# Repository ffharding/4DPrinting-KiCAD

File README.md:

# 4DPrinting KiCAD Repository
The objective of the repository is to store the files needed to implement KiCAD automating into the design flow of the 4DPrinting project, including code to automatically generate files and custom components.

## Features 
### 1. kicad-import
This features consist on the code required to import the user input such as the components chosen by the user, the desired placement of these components and the information that relate the components (what the final PCB is designed for). The output of this feature is the base KICAD file that starts the automating design flow.
### 2. autorouting
Autoroute the PCB created using the freerouting open source module and automate the creation of the finished PCB that will be printed.
### 3. xml-generator
Generate an XML file with the already finished and autorouted PCB for better data management.
### 4. gcode-generator
Generate GCODE from the XML file with PCB data.

## Components
### 4DPrinting.pretty
The .pretty folder is a KiCAD library containing custom component footprints created for the base schematic of the projcet, inlcuding components designed to be printed and those components that were modified to fit the specifications of the project (through hole to surface mount components). 

| Component      | Description |
| ------------- |:-------------:|
| Battery.kicad_mod      | Footprint for battery cell pack connected with flywires to +/- pads     |
| MODULE_ESP-M2.kicad_mod      | Footprint for ESP-M2 wifi chip downloaded from SnapEDA: https://www.snapeda.com/parts/ESP-M2/Doctors%20of%20Intelligence%20%26%20Technology%20Co.%2C%20LTD/view-part/?ref=search&t=%20ESP-M2%20    |
| TPU.kicad_mod      | Footprint for printed unit TPU   |
| charge_port.kicad_mod      | Footprint for 3.5mm charging port for battery   |
| custom_lf356.kicad_mod      | Footprint for LF356 chip converted to surface mount device |
| switch.kicad_mod      | Footprint for push button switch |
| voltage_regulator.kicad_mod      | Footprint for LD1117v33 voltage regulator converted to surface mount device |

## Installation
Clone repository into local machine using the following commmands in terminal or Git Bash:
```
git clone https://github.com/ffharding/4DPrinting-KiCAD.git
```
More information into Git repositories can be found on the [offical Git documentation](https://docs.github.com/en/repositories).

After cloning the repository and installing the required software([KiCAD 6.0](https://www.kicad.org/download/) and [freerouting](https://github.com/freerouting/freerouting/releases
)), open the plugin directory from KiCAD using the instructions included in the documentation folder and copy the source code of the feature to test.

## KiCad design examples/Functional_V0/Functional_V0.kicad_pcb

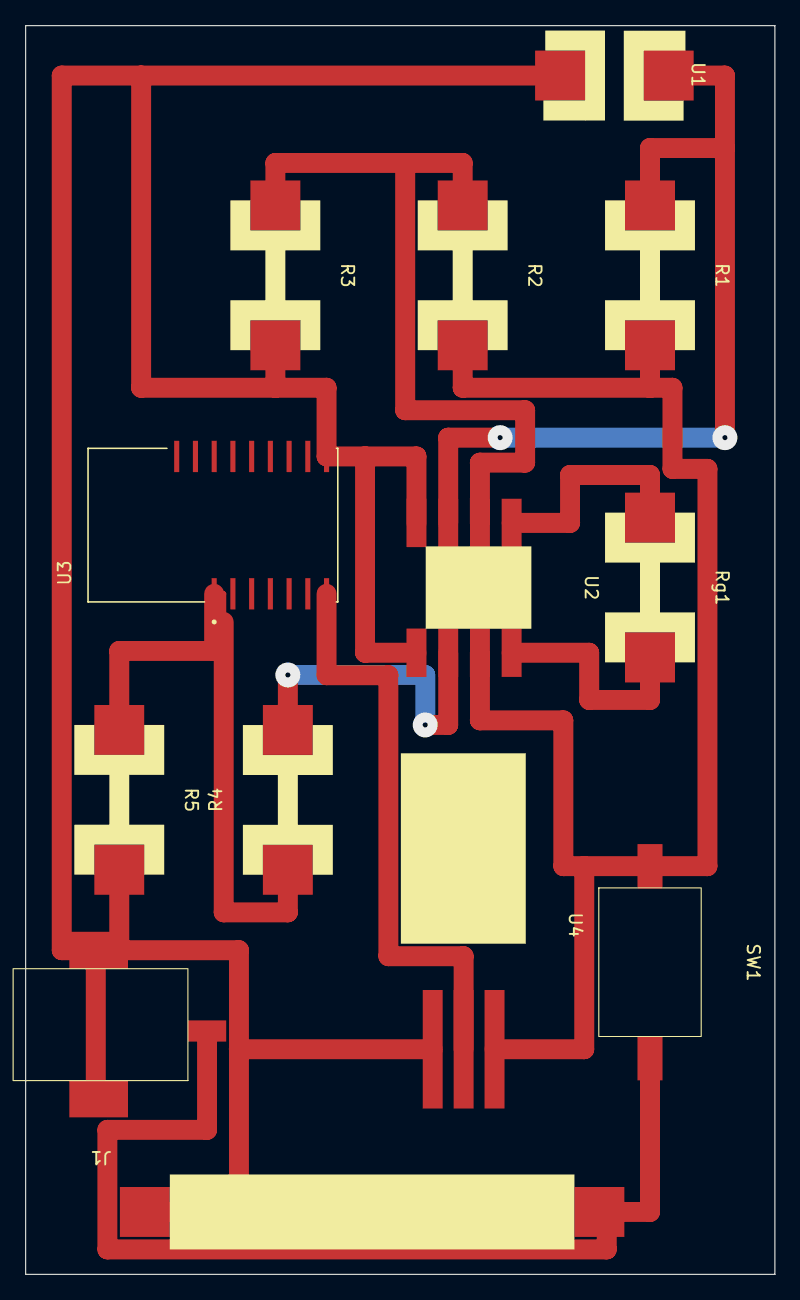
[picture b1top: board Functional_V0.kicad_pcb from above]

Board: 2 copper layers, 60.0 x 100.0 mm, 13 parts (0 on the bottom side), 10 nets.

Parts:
BT1: Battery
J1: charge_port
R1, R2, R3, R4, R5: TPU
Rg1: TPU
SW1: switch
U1: for_thing; wave_gen
U2: dummy_lf356; custom_lf356
U3: MODULE_ESP-M2
U4: voltage_regulator

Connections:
unnamed: BT1.1, J1.1, SW1.2
unnamed: BT1.2, J1.2, J1.3, R3.2, R5.2, U1.1, U2.4, U2.5, U3.8, U4.1
unnamed: R1.1, U1.2, U2.3
unnamed: R1.2, R2.2, SW1.1, U2.7, U4.3
unnamed: R2.1, R3.1, U2.2
unnamed: R4.1, R5.1, U3.1
unnamed: R4.2, U2.6
unnamed: Rg1.1, U2.1
unnamed: Rg1.2, U2.8
unnamed: U3.7, U4.2

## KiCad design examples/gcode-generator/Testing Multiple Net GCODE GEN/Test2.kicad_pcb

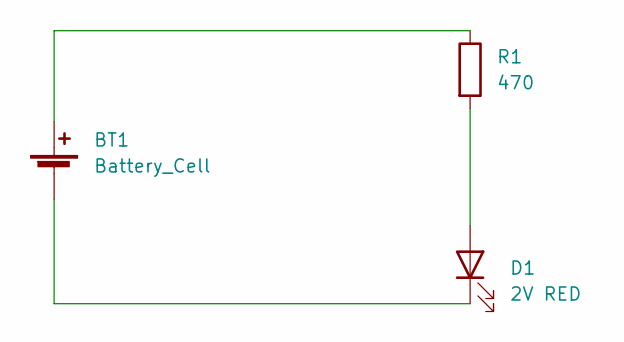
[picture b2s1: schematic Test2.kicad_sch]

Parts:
BT1: Battery_Cell; BatteryHolder_Keystone_1058_1x2032
D1: 2V RED; LED_0603_1608Metric
R1: 470; R_0402_1005Metric

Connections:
unnamed: BT1.2 (-), D1.1 (K)
unnamed: D1.2 (A), R1.2
unnamed: BT1.1 (+), R1.1

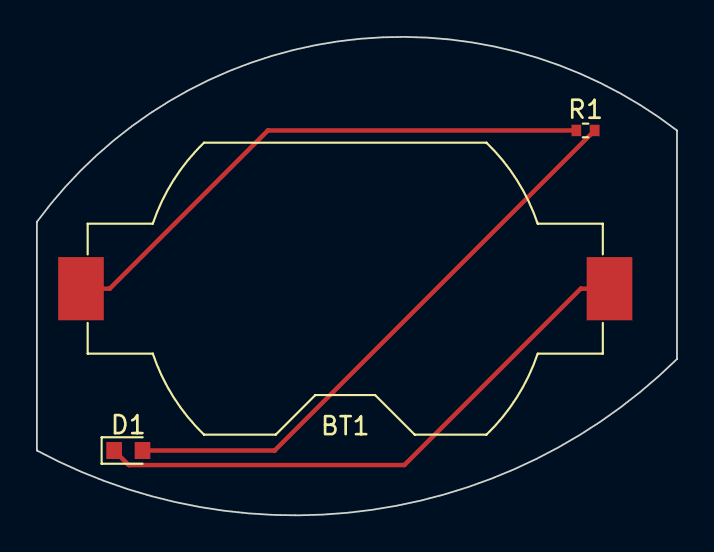
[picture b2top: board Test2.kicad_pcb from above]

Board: 2 copper layers, 35.6 x 26.6 mm, 3 parts (0 on the bottom side), 3 nets.

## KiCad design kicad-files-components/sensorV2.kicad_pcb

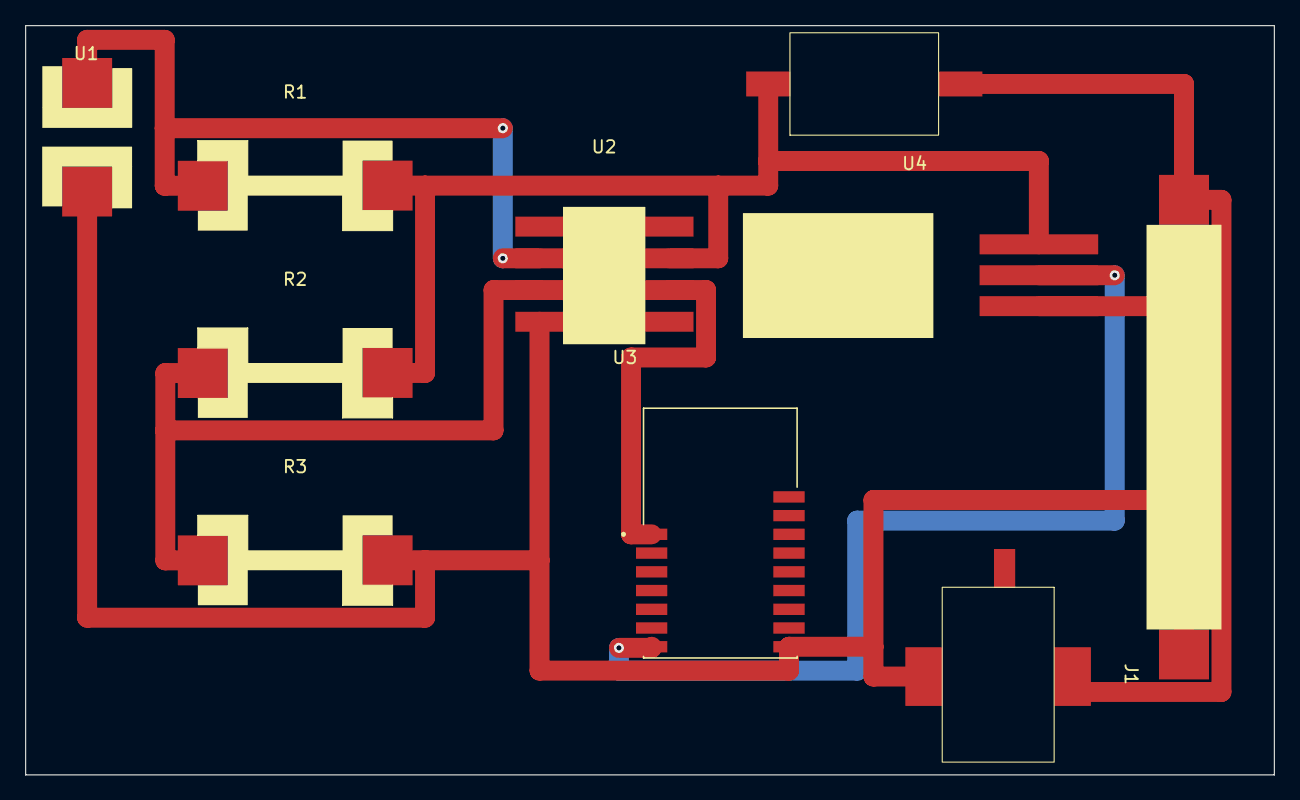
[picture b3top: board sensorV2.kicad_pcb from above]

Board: 2 copper layers, 100.0 x 60.0 mm, 10 parts (0 on the bottom side), 7 nets.

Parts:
BT1: Battery
J1: Jack-DC; charge_port
R1, R2, R3: R; TPU
SW1: SW_Push; switch
U1: thing; for_thing
U2: LF356; dummy_lf356
U3: ESP-M2; MODULE_ESP-M2
U4: LD1117V33; voltage_regulator

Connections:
unnamed: BT1.1 (+), J1.2, SW1.2
unnamed: BT1.2 (-), J1.1, R3.2, U1.1, U2.4 (V-), U3.8 (GND), U4.1 (ADJ/GND)
unnamed: R1.1, U1.2, U2.2 (-)
unnamed: R1.2, R2.2, SW1.1, U2.7 (V+), U4.3 (VIN)
unnamed: R2.1, R3.1, U2.3 (+)
unnamed: U2.6, U3.1 (ADC)
unnamed: U3.7 (VCC), U4.2 (VOUT)

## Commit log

2023-05-17 Create repository and README
2023-05-18 Add base KiCAD files and custom components
2023-05-18 Updated main branch with working KiCAD Implementation, missing READMEs for individual folders/features
2023-05-19 Added symbol library to kicad-files-components
2023-05-19 Updated test_net_fix
2023-05-19 Final setup files to main
2023-05-23 Created component_parser
2023-05-23 Added documentation folder
2023-05-23 Added first installation instructions and fixed redundancies
2023-05-24 Uncomplte work in component_parser
2023-05-24 Separated source code with exmaples, created examples folder
2023-05-25 Finished plotting for test_net_fix, needs cleanup
2023-05-26 Finished component parser
2023-05-26 Added class comments to test_net_fix
2023-06-07 Minor updates to net_parser
2023-06-08 First updpate to GCODE Generator
2023-06-13 Basic GCODE generator pipeline complete
2023-06-13 Structure overhaul and basic GCODE generation
2023-06-16 Working version for routed KiCAD to GCODE
2023-06-19 Update to main GCODE generator functionality and autoruoting testing
2023-06-19 Updated instructions
2023-06-22 Working version with correct autorouting
2023-06-22 Updated branch, started working on fixing rotation bug
2023-06-23 Working version with autorouting to one GCODE file
2023-06-27 Working version with double output layers, needs optimization in printing
2023-06-28 Optimized double layer GCODE
2023-06-29 Updated instructions for GCODE gen
2023-06-29 Cleaned up branch
2023-06-29 First changes to TPU component
2023-07-06 Added estrusion head config, optimized gcode generation
2023-07-11 Updated with comments and code clean up
2023-07-14 Created kicad_import functionality (import components and netlist)
2023-07-21 Import board functionality beta finished
2023-07-27 Finished KICAD import functionality:
2023-07-28 GCODE updates and minor bug fixes
2023-07-29 Updated GCODE up to specifications
2023-08-10 Final changes and fixes to code
2023-08-10 Documentation changes and path fixes
2023-08-17 Creation of PNP GCODE, first version untested
2023-08-18 Updated instruction manual
2023-10-21 Functional Circuit Test
